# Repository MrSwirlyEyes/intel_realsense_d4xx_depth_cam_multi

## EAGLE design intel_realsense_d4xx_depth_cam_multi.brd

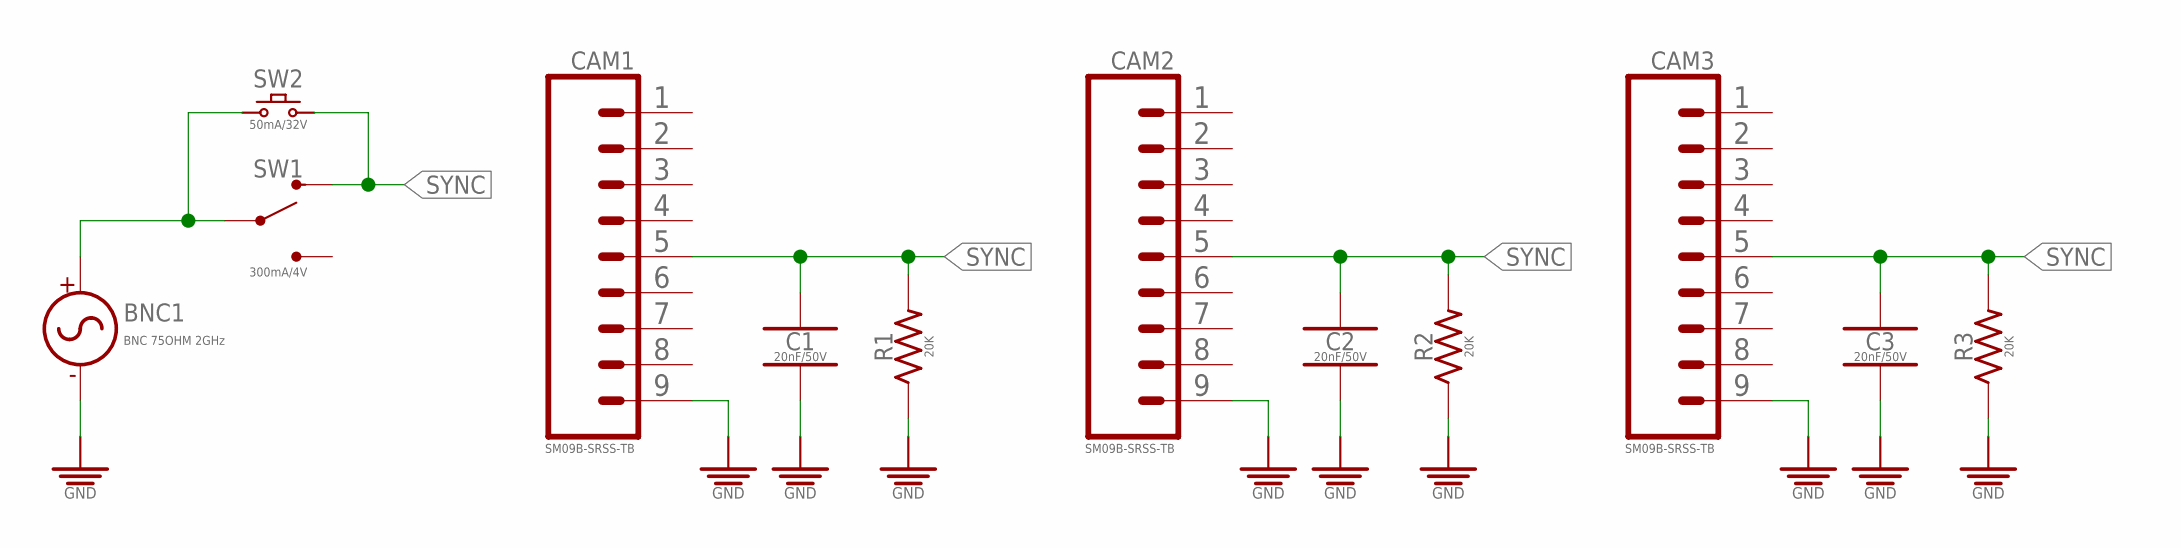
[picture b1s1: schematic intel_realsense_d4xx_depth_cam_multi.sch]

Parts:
BNC1: BNC 75OHM 2GHz; BNC_RA_1-1337543-0
C1, C2, C3: 20nF/50V; CAPC1608X95
CAM1, CAM2, CAM3: SM09B-SRSS-TB
R1, R2, R3: 20K; RESC1608X65_SMD-0603
SW1: 300mA/4V; SW_SLIDE_SPDT_RA_SMD_4V_300MA_6.7L-2.6W
SW2: 50mA/32V; BTN_MOMENTARY_SPDT-NO_L4.6-W2.8

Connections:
GND: BNC1.-, C1.2, C2.2, C3.2, CAM1.9, CAM2.9, CAM3.9, R1.1, R2.1, R3.1
unnamed: BNC1.+, SW1.2, SW2.2 (1)
SYNC: C1.1, C2.1, C3.1, CAM1.5, CAM2.5, CAM3.5, R1.2, R2.2, R3.2, SW1.1 (S1), SW2.3 (2)

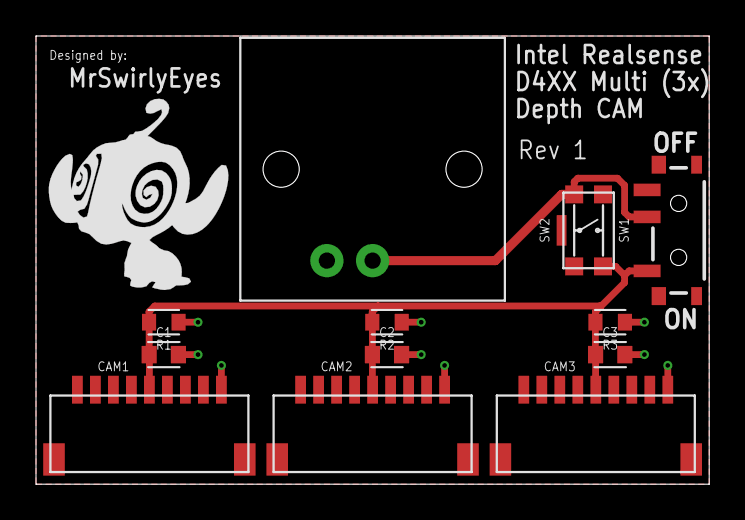
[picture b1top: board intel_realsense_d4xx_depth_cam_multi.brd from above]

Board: 2 copper layers, 37.4 x 24.9 mm, 14 parts (1 on the bottom side), 3 nets.

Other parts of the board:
U$4, U$5: MRSWIRLYEYES-LOGO

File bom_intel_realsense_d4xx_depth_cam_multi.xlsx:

Qty | Value | Device | Parts | DIST | DISTLINK | DISTPN
10 | 20K | 20KŒ©_SMD-0603_1/10W-5% | R1, R2, R3 | Digikey | https://www.digikey.com/products/en?keywords=P20KGCT-ND | P20KGCT-ND
10 | 20nF/50V | 22NF_CER_SMD-0603_50V-10% | C1, C2, C3 | Digikey | https://www.digikey.com/products/en?keywords=445-2505-1-ND | 445-2505-1-ND
5 | 300mA/4V | SWITCH_SPDT_RA_SMD_300MA-4V_6.7L-2.6W | SW1 | Digikey | https://www.digikey.com/products/en?keywords=679-1847-1-ND | 679-1847-1-ND
5 | 50mA/32V | SWITCH_MOMENTARY_SPST-NO_SMD_50MA-32V_L4.6-W2.8 | SW2 | Digikey | https://www.digikey.com/products/en?keywords=401-1426-1-ND | 401-1426-1-ND
5 | BNC 75OHM 2GHz | BNC_CONNECTOR_PTH_75OHM_2GHZ | BNC1 | Digikey | https://www.digikey.com/products/en?keywords=A97560-ND | A97560-ND
10 | SM09B-SRSS-TB | 1X09_SM09B-SRSS-TB CONNECTOR | CAM1, CAM2, CAM3 | Digikey | https://www.digikey.com/products/en?keywords=455-1809-1-ND | 455-1809-1-ND
10 | SM09B-SRSS-TB | 1X09_SM09B-SRSS-TB HOUSING | CAM1, CAM2, CAM3 | Digikey | https://www.digikey.com/products/en?keywords=455-1399-ND | 455-1399-ND
25 | SM09B-SRSS-TB | 1X09_SM09B-SRSS-TB CRIMP | CAM1, CAM2, CAM3 | Digikey | https://www.digikey.com/products/en?keywords=455-1561-1-ND | 455-1561-1-ND
1 | BNC 75OHM 2GHz | Hosa BNC-59-106 BNC to BNC 75-Ohm Coax Cable, 6 feet | BNC1 | Amazon | https://www.amazon.com/Hosa-BNC-59-106-75-Ohm-Coax-Cable/dp/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 | B000068OFC
1 | PCB | PCB (package of 3) | PCB | OSH Park | https://oshpark.com/shared_projects/JmvUitl9 | N/A

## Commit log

2018-10-29 initialize repo for intel realsense d4xx depth camera multi-cam PCB.
2018-10-29 Add gitignore to ignore EAGLE swap files.
2018-10-29 Rev 1: Board complete.
2018-10-30 Add 22nF cap and 20K resistor.
2018-11-03 Add BOM for intel depth cam.
2018-12-18 Add schematic as a PNG.
